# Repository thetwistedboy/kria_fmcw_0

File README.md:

# kria_fmcw_0
Carrier for Kria K24 SoM. Hardware to support FMCW radar playing.

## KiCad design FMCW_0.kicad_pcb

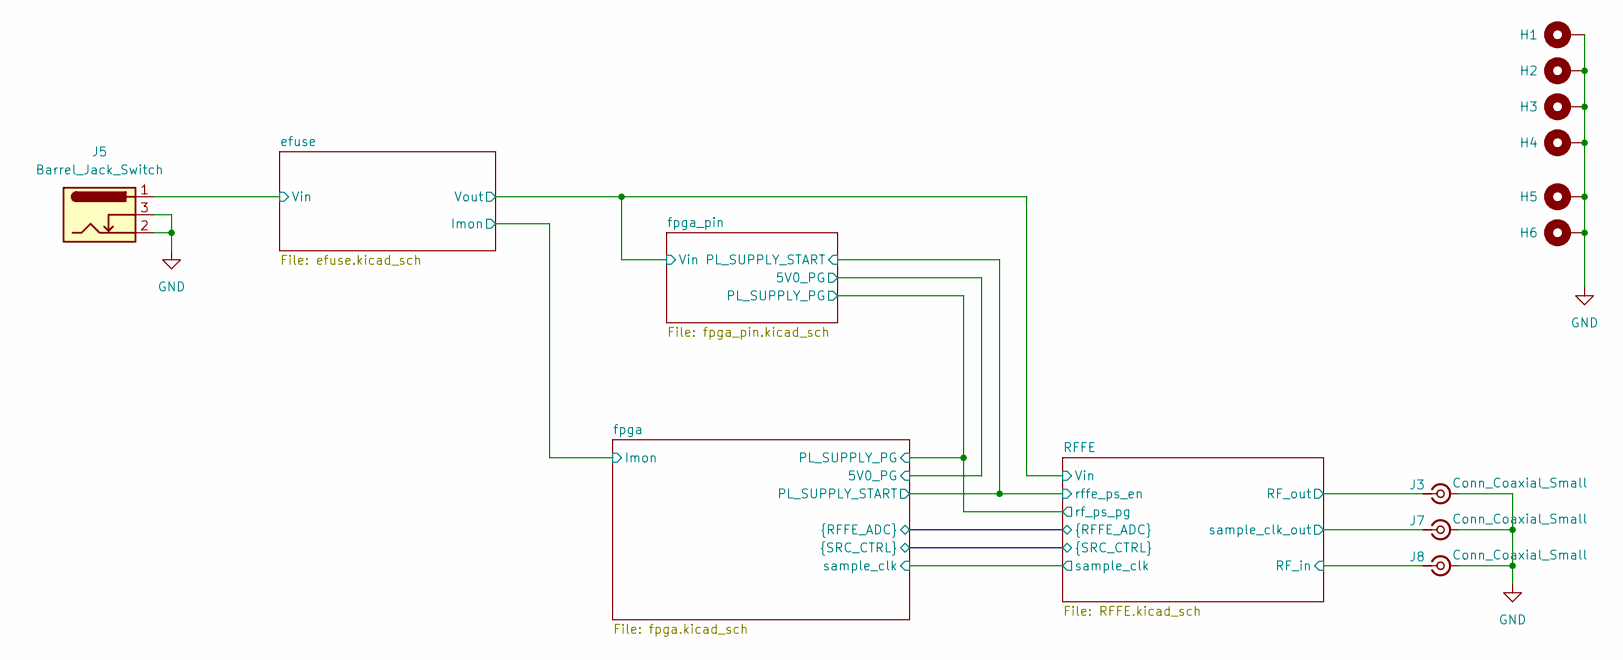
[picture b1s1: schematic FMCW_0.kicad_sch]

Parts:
H1, H2, H3, H4, H5, H6: MountingHole_Pad; MountingHole_3.2mm_M3_DIN965_Pad
J3, J7, J8: Conn_Coaxial_Small; SMA_Samtec_SMA-J-P-H-ST-EM1_EdgeMount
J5: Barrel_Jack_Switch; BarrelJack_Wuerth_6941xx301002; Digikey PN 732-5934-ND

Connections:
/RFFE/RF_in: J8.1 (In); also elsewhere on the board
/RFFE/RF_out: J3.1 (In); also elsewhere on the board
/RFFE/sample_clk_out: J7.1 (In); also elsewhere on the board
/efuse/Vin: J5.1; also elsewhere on the board
GND: H1.1 (1_1), H2.1 (1_1), H3.1 (1_1), H4.1 (1_1), H5.1 (1_1), H6.1 (1_1), J3.2 (Ext), J5.2, J5.3, J7.2 (Ext), J8.2 (Ext); also elsewhere on the board

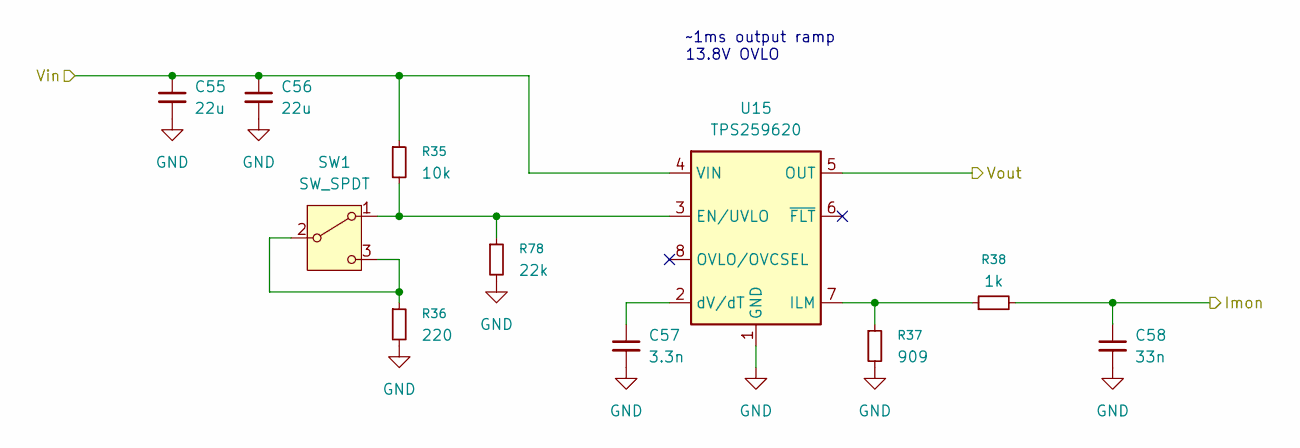
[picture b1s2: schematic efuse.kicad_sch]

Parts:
C55, C56: 22u; C_0805_2012Metric; Digikey PN 587-6359-1-ND
C57: 3.3n; C_0402_1005Metric; Digikey PN 1276-1552-1-ND
C58: 33n; C_0402_1005Metric; Digikey PN 587-3466-1-ND
R35: 10k; R_0402_1005Metric; Digikey PN RMCF0402FT10K0CT-ND
R36: 220; R_0402_1005Metric; Digikey PN 311-220LRCT-ND
R37: 909; R_0402_1005Metric; Digikey PN YAG3256CT-ND
R38: 1k; R_0402_1005Metric; Digikey PN 311-1.00KLRCT-ND
R78: 22k; R_0402_1005Metric; Digikey PN RMCF0402FT10K0CT-ND
SW1: SW_SPDT; SW_Slide_SPDT_Angled_CK_OS102011MA1Q; Digikey PN CKN9559-ND
U15: TPS259620; TI_SO-PowerPAD-8; Digikey PN 296-TPS259620DDARCT-ND

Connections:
/RFFE/Vin: U15.5 (OUT); also elsewhere on the board
/efuse/Imon: C58.1, R38.2; also elsewhere on the board
/efuse/Vin: C55.1, C56.1, R35.1, U15.4 (VIN); also elsewhere on the board
GND: C55.2, C56.2, C57.2, C58.2, R36.2, R37.2, R78.2, U15.1 (GND), U15.9 (GND); also elsewhere on the board
unnamed: R35.2, R78.1, SW1.1 (A), U15.3 (EN/UVLO)
unnamed: R36.1, SW1.2 (B), SW1.3 (C)
unnamed: R37.1, R38.1, U15.7 (ILM)
unnamed: C57.1, U15.2 (dV/dT)

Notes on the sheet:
~1ms output ramp 13.8V OVLO

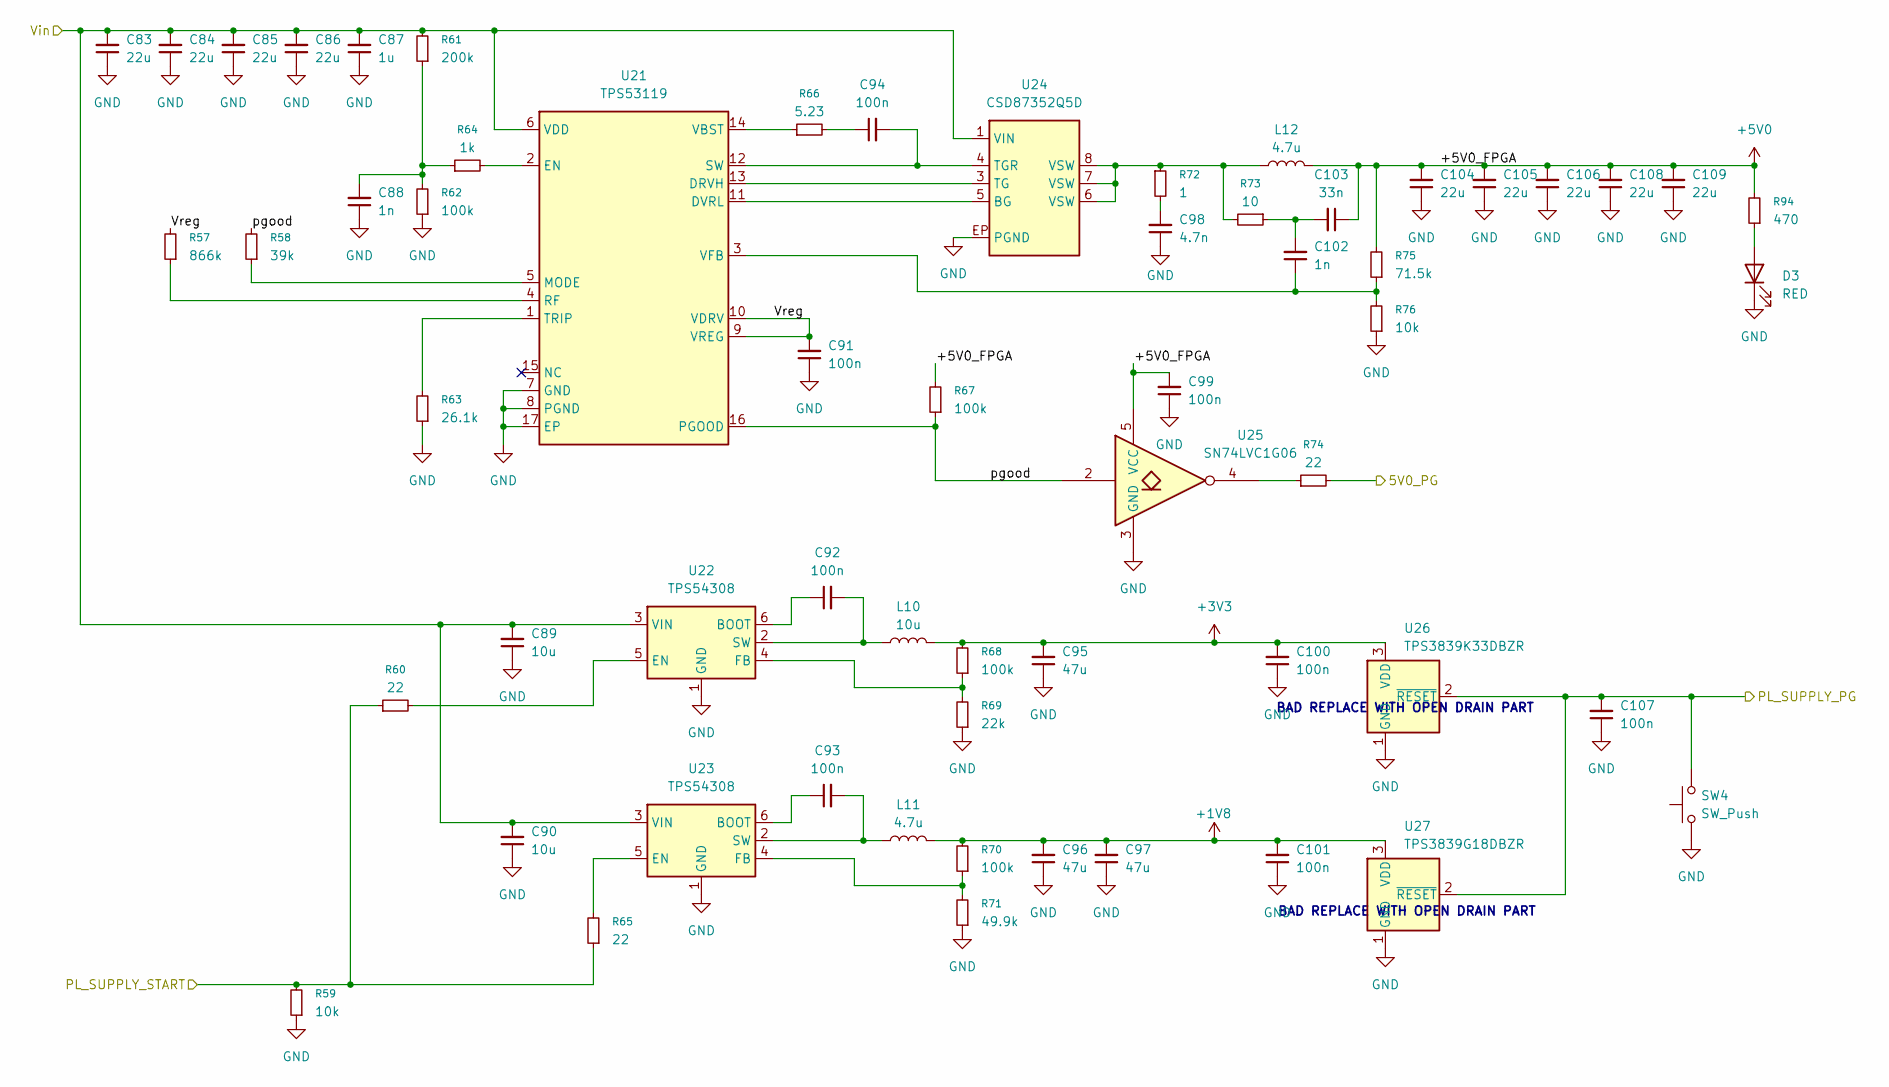
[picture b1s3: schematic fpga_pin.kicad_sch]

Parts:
C83, C84, C85, C86: 22u; C_1210_3225Metric; Digikey PN 587-5951-1-ND
C87: 1u; C_0402_1005Metric; Digikey PN 1276-1067-1-ND
C88, C102: 1n; C_0402_1005Metric; Digikey PN 490-3244-1-ND
C89, C90: 10u; C_0603_1608Metric; Digikey PN 490-7202-1-ND
C91, C92, C93, C94, C99, C100, C101, C107: 100n; C_0402_1005Metric; Digikey PN 1276-1043-1-ND
C95, C96, C97: 47u; C_0805_2012Metric; Digikey PN 490-13249-1-ND
C98: 4.7n; C_0402_1005Metric; Digikey PN 490-1308-1-ND
C103: 33n; C_0402_1005Metric; Digikey PN 587-3466-1-ND
C104, C105, C106, C108, C109: 22u; C_0805_2012Metric; Digikey PN 587-5466-1-ND
D3: RED; LED_0603_1608Metric; Digikey PN 160-1436-1-ND
L10: 10u; L_Wuerth_MAPI-4030; Digikey PN 732-11206-1-ND
L11: 4.7u; L_Wuerth_MAPI-4020; Digikey PN 732-11316-1-ND
L12: 4.7u; L_Wuerth_XHMI-6060; Digikey PN 732-744393445047CT-ND
R57: 866k; R_0402_1005Metric; Digikey PN RMCF0402FT866KCT-ND
R58: 39k; R_0402_1005Metric; Digikey PN 311-39.0KLRCT-ND
R59, R76: 10k; R_0402_1005Metric; Digikey PN RMCF0402FT10K0CT-ND
R60, R65, R74: 22; R_0402_1005Metric; Digikey PN 541-22.0LCT-ND
R61: 200k; R_0402_1005Metric; Digikey PN 311-200KLRCT-ND
R62, R67, R68, R70: 100k; R_0402_1005Metric; Digikey PN 311-100KLRCT-ND
R63: 26.1k; R_0402_1005Metric; Digikey PN 311-26.1KLRCT-ND
R64: 1k; R_0402_1005Metric; Digikey PN 311-1.00KLRCT-ND
R66: 5.23; R_0402_1005Metric; Digikey PN 541-5.23LLCT-ND
R69: 22k; R_0402_1005Metric; Digikey PN RMCF0402FT10K0CT-ND
R71: 49.9k; R_0402_1005Metric; Digikey PN P49.9KLCT-ND
R72: 1; R_0402_1005Metric; Digikey PN 541-1.00LLCT-ND
R73: 10; R_0402_1005Metric; Digikey PN 311-10.0LRCT-ND
R75: 71.5k; R_0402_1005Metric; Digikey PN RMCF0402FT71K5CT-ND
R94: 470; R_0402_1005Metric; Digikey PN 311-470LRCT-ND
SW4: SW_Push; SW_Push_1P1T_NO_CK_KMR2; Digikey PN 108-KMR211GLFSCT-ND
U21: TPS53119; VQFN-16-1EP_3x3mm_P0.5mm_EP1.45x1.45mm; Digikey PN 296-51985-1-ND
U22, U23: TPS54308; SOT-23-6; Digikey PN 296-46237-1-ND
U24: CSD87352Q5D; Texas_8-LSON_5x6mm; Digikey PN 296-29161-1-ND
U25: SN74LVC1G06; SOT-353_SC-70-5; Digikey PN 296-8484-1-ND
U26: TPS3839K33DBZR; SOT-23; Digikey PN 296-35471-1-ND
U27: TPS3839G18DBZR; SOT-23; Digikey PN 296-40761-1-ND

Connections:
+1V8: C96.2, C97.2, C101.2, L11.2, R70.2, U27.3 (VDD); also elsewhere on the board
+3V3: C95.2, C100.2, L10.2, R68.2, U26.3 (VDD); also elsewhere on the board
+5V0: C99.2, C103.1, C104.2, C105.2, C106.2, C108.2, C109.2, L12.2, R67.2, R75.2, R94.2, U25.5 (VCC); also elsewhere on the board
/RFFE/Vin: C83.2, C84.2, C85.2, C86.2, C87.2, C89.2, C90.2, R61.2, U21.6 (VDD), U22.3 (VIN), U23.3 (VIN), U24.1 (VIN); also elsewhere on the board
/RFFE/rf_ps_pg: C107.2, SW4.2, U26.2 (~RESET), U27.2 (~RESET); also elsewhere on the board
/RFFE/rffe_ps_en: R59.2, R60.1, R65.1; also elsewhere on the board
/fpga/5V0_PG: R74.2; also elsewhere on the board
/fpga_pin/Vreg: C91.2, R57.2, U21.9 (VREG), U21.10 (VDRV)
/fpga_pin/pgood: R58.2, R67.1, U21.16 (PGOOD), U25.2
GND: C83.1, C84.1, C85.1, C86.1, C87.1, C88.1, C89.1, C90.1, C91.1, C95.1, C96.1, C97.1, C98.1, C99.1, C100.1, C101.1, C104.1, C105.1, C106.1, C107.1, C108.1, C109.1, D3.1 (K), R59.1, R62.1, R63.1, R69.1, R71.1, R76.1, SW4.1, U21.7 (GND), U21.8 (PGND), U21.17 (EP), U22.1 (GND), U23.1 (GND), U24.EP (PGND), U25.3 (GND), U26.1 (GND), U27.1 (GND); also elsewhere on the board
unnamed: C88.2, R61.1, R62.2, R64.1
unnamed: C94.1, R66.2
unnamed: C98.2, R72.2
unnamed: C102.2, C103.2, R73.1
unnamed: D3.2 (A), R94.1
unnamed: L12.1, R72.1, R73.2, U24.6 (VSW), U24.7 (VSW), U24.8 (VSW)
unnamed: R74.1, U25.4
unnamed: U21.13 (DRVH), U24.3 (TG)
unnamed: U21.11 (DVRL), U24.5 (BG)
unnamed: R64.2, U21.2 (EN)
unnamed: R58.1, U21.5 (MODE)
unnamed: R57.1, U21.4 (RF)
unnamed: C94.2, U21.12 (SW), U24.4 (TGR)
unnamed: R63.2, U21.1 (TRIP)
unnamed: R66.1, U21.14 (VBST)
unnamed: C102.1, R75.1, R76.2, U21.3 (VFB)
unnamed: C92.1, U22.6 (BOOT)
unnamed: R60.2, U22.5 (EN)
unnamed: R68.1, R69.2, U22.4 (FB)
unnamed: C92.2, L10.1, U22.2 (SW)
unnamed: C93.1, U23.6 (BOOT)
unnamed: R65.2, U23.5 (EN)
unnamed: R70.1, R71.2, U23.4 (FB)
unnamed: C93.2, L11.1, U23.2 (SW)

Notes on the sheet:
BAD REPLACE WITH OPEN DRAIN PART

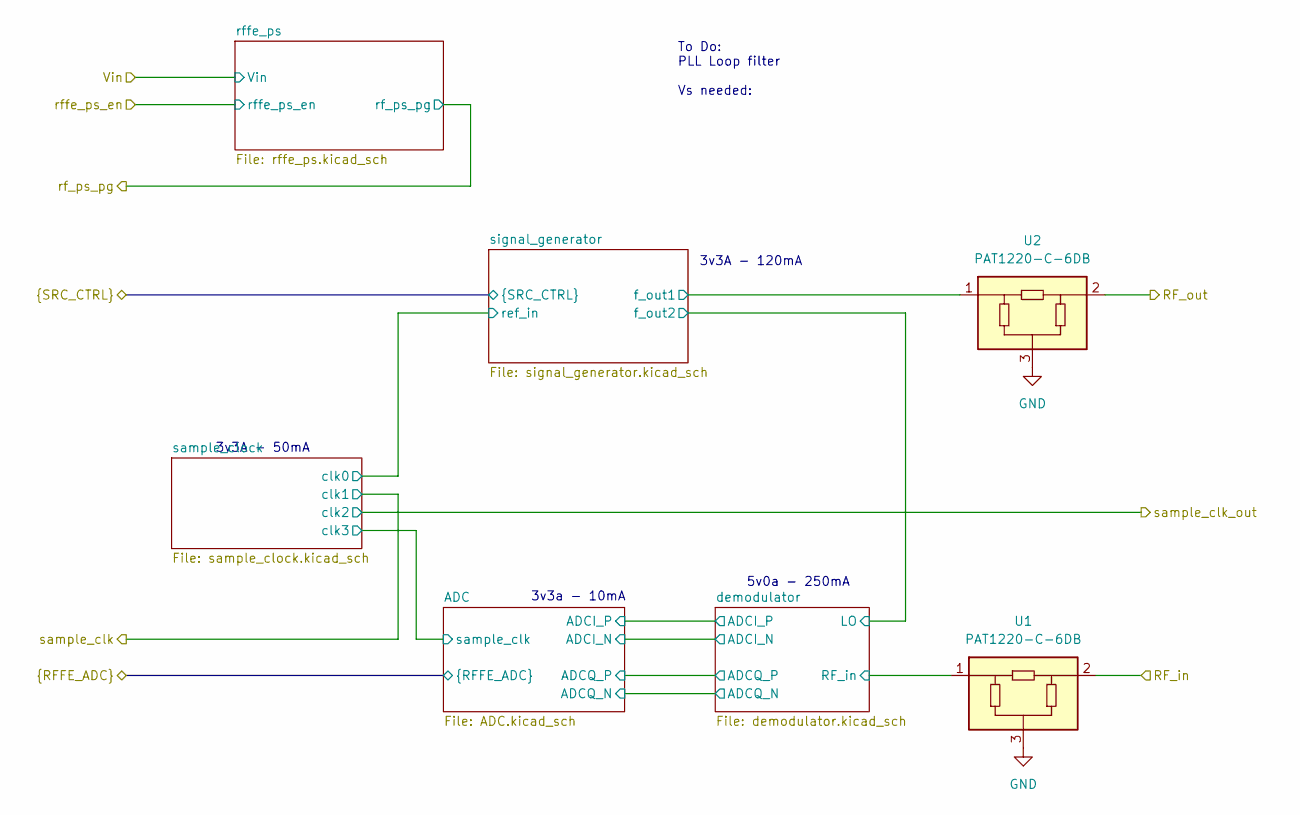
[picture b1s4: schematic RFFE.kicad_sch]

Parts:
U1, U2: PAT1220-C-6DB; RF_Attenuator_Susumu_PAT1220; Digikey PN PAT126CT-ND

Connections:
/RFFE/RF_in: U1.2; also elsewhere on the board
/RFFE/RF_out: U2.2; also elsewhere on the board
/RFFE/demodulator/RF_in: U1.1; also elsewhere on the board
/RFFE/signal_generator/f_out1: U2.1; also elsewhere on the board
GND: U1.3, U2.3; also elsewhere on the board

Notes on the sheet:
5v0a - 250mA
To Do: PLL Loop filter Vs needed:
3v3A - 50mA
3v3A - 120mA
3v3a - 10mA

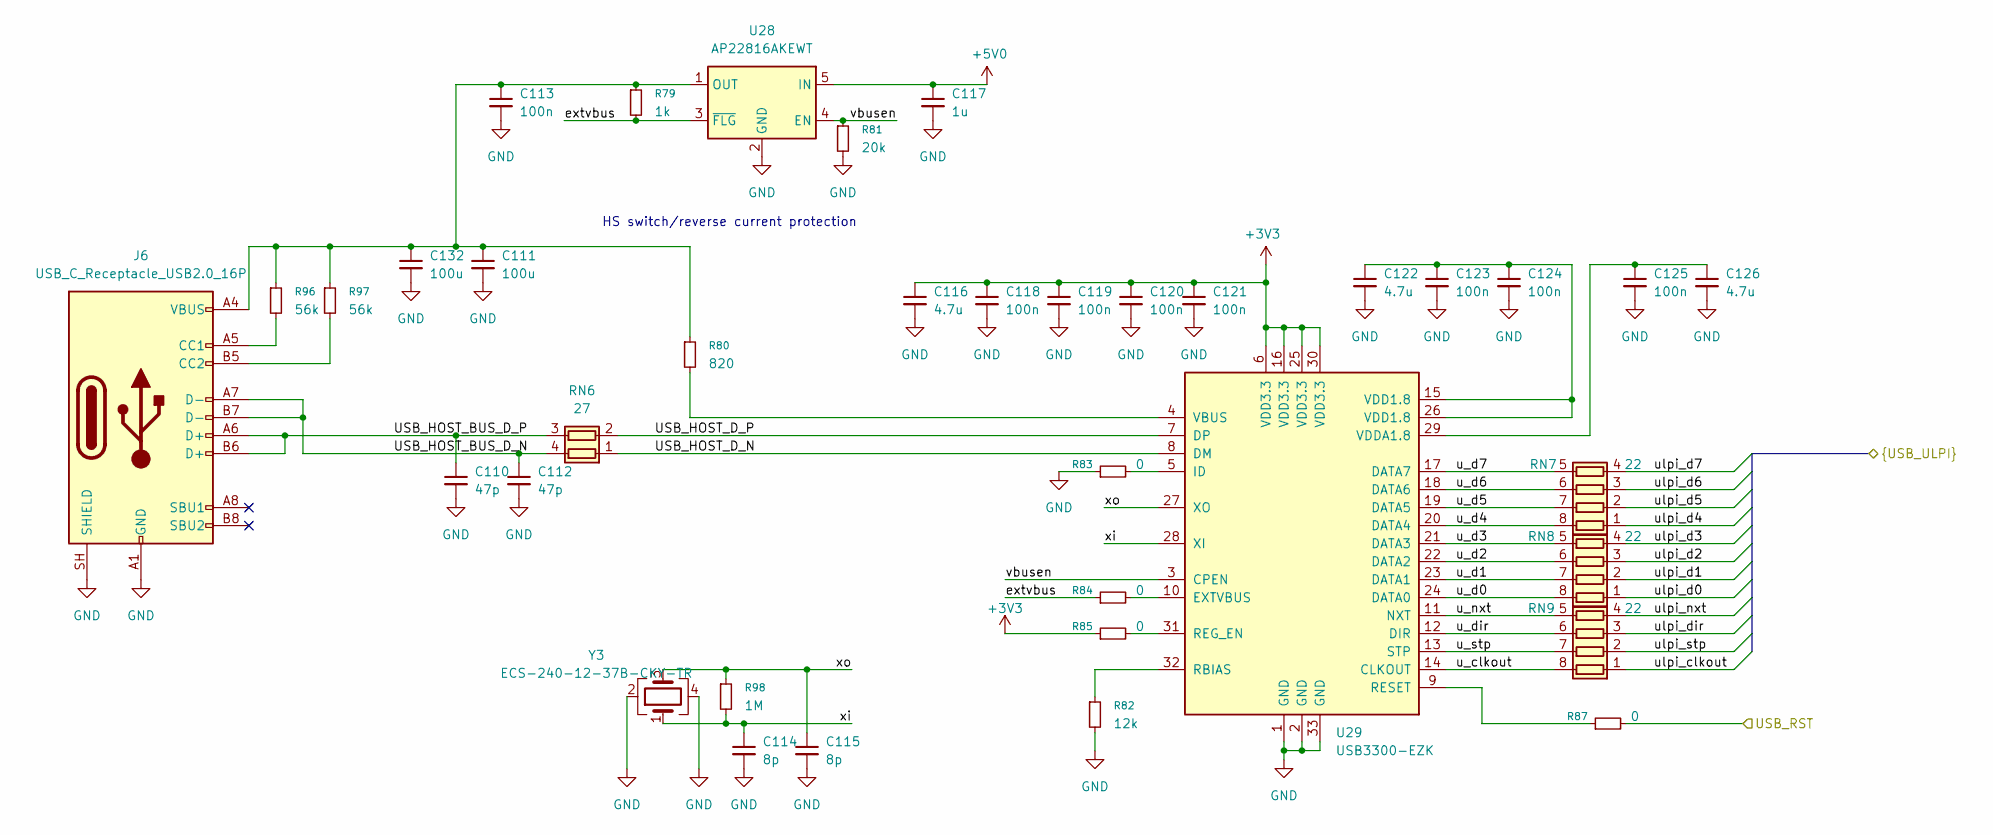
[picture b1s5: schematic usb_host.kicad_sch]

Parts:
C110, C112: 47p; C_0402_1005Metric; Digikey PN 490-5942-1-ND
C111, C132: 100u; C_1210_3225Metric; Digikey PN 490-10534-1-ND
C113, C118, C119, C120, C121, C123, C124, C125: 100n; C_0402_1005Metric; Digikey PN 1276-1043-1-ND
C114, C115: 8p; C_0402_1005Metric; Digikey PN 1276-CL05C080DB51PNCCT-ND
C116, C122, C126: 4.7u; C_0402_1005Metric; Digikey PN 490-14306-1-ND
C117: 1u; C_0402_1005Metric; Digikey PN 1276-1067-1-ND
J6: USB_C_Receptacle_USB2.0_16P; USB_C_Receptacle_GCT_USB4105-xx-A_16P_TopMnt_Horizontal; Digikey PN 2073-USB4215-03-ACT-ND
R79: 1k; R_0402_1005Metric; Digikey PN 311-1.00KLRCT-ND
R80: 820; R_0402_1005Metric; Digikey PN 311-820LRCT-ND
R81: 20k; R_0402_1005Metric; Digikey PN 311-20.0KLRCT-ND
R82: 12k; R_0402_1005Metric; Digikey PN 311-12.0KLRCT-ND
R83, R84, R85, R87: 0; R_0402_1005Metric; Digikey PN 311-0.0JRCT-ND
R96, R97: 56k; R_0402_1005Metric; Digikey PN 311-20.0KLRCT-ND
R98: 1M; R_0402_1005Metric; Digikey PN 311-1.00MLRCT-ND
RN6: 27; R_Array_Convex_2x0402; Digikey PN Y5270CT-ND
RN7, RN8, RN9: 22; R_Array_Convex_4x0402; Digikey PN Y7220CT-ND
U28: AP22816AKEWT; SOT-23-5; Digikey PN 31-AP22816AKEWT-7CT-ND
U29: USB3300-EZK; QFN-32-1EP_5x5mm_P0.5mm_EP3.45x3.45mm; Digikey PN 638-1034-ND
Y3: ECS-240-12-37B-CKY-TR; Crystal_SMD_2016-4Pin_2.0x1.6mm; Digikey PN XC3064TR-ND

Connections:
+3V3: C116.1, C118.1, C119.1, C120.1, C121.1, R85.1, U29.6 (VDD3.3), U29.16 (VDD3.3), U29.25 (VDD3.3), U29.30 (VDD3.3); also elsewhere on the board
+5V0: C117.1, U28.5 (IN); also elsewhere on the board
/fpga/fpga_ja/ulpi_clkout: RN9.1 (R1.1); also elsewhere on the board
/fpga/fpga_ja/ulpi_d0: RN8.1 (R1.1); also elsewhere on the board
/fpga/fpga_ja/ulpi_d1: RN8.2 (R2.1); also elsewhere on the board
/fpga/fpga_ja/ulpi_d2: RN8.3 (R3.1); also elsewhere on the board
/fpga/fpga_ja/ulpi_d3: RN8.4 (R4.1); also elsewhere on the board
/fpga/fpga_ja/ulpi_d4: RN7.1 (R1.1); also elsewhere on the board
/fpga/fpga_ja/ulpi_d5: RN7.2 (R2.1); also elsewhere on the board
/fpga/fpga_ja/ulpi_d6: RN7.3 (R3.1); also elsewhere on the board
/fpga/fpga_ja/ulpi_d7: RN7.4 (R4.1); also elsewhere on the board
/fpga/fpga_ja/ulpi_dir: RN9.3 (R3.1); also elsewhere on the board
/fpga/fpga_ja/ulpi_nxt: RN9.4 (R4.1); also elsewhere on the board
/fpga/fpga_ja/ulpi_stp: RN9.2 (R2.1); also elsewhere on the board
/fpga/fpga_ja/usb_reset: R87.2; also elsewhere on the board
/fpga/usb_host/USB_HOST_BUS_D_N: C112.1, J6.A7 (D-), J6.B7 (D-), RN6.4 (R1.2)
/fpga/usb_host/USB_HOST_BUS_D_P: C110.1, J6.A6 (D+), J6.B6 (D+), RN6.3 (R2.2)
/fpga/usb_host/USB_HOST_D_N: RN6.1 (R1.1), U29.8 (DM)
/fpga/usb_host/USB_HOST_D_P: RN6.2 (R2.1), U29.7 (DP)
/fpga/usb_host/extvbus: R79.2, R84.1, U28.3 (~FLG)
/fpga/usb_host/u_clkout: RN9.8 (R1.2), U29.14 (CLKOUT)
/fpga/usb_host/u_d0: RN8.8 (R1.2), U29.24 (DATA0)
/fpga/usb_host/u_d1: RN8.7 (R2.2), U29.23 (DATA1)
/fpga/usb_host/u_d2: RN8.6 (R3.2), U29.22 (DATA2)
/fpga/usb_host/u_d3: RN8.5 (R4.2), U29.21 (DATA3)
/fpga/usb_host/u_d4: RN7.8 (R1.2), U29.20 (DATA4)
/fpga/usb_host/u_d5: RN7.7 (R2.2), U29.19 (DATA5)
/fpga/usb_host/u_d6: RN7.6 (R3.2), U29.18 (DATA6)
/fpga/usb_host/u_d7: RN7.5 (R4.2), U29.17 (DATA7)
/fpga/usb_host/u_dir: RN9.6 (R3.2), U29.12 (DIR)
/fpga/usb_host/u_nxt: RN9.5 (R4.2), U29.11 (NXT)
/fpga/usb_host/u_stp: RN9.7 (R2.2), U29.13 (STP)
/fpga/usb_host/vbusen: R81.1, U28.4 (EN), U29.3 (CPEN)
/fpga/usb_host/xi: C114.1, R98.2, U29.28 (XI), Y3.1
/fpga/usb_host/xo: C115.1, R98.1, U29.27 (XO), Y3.3
GND: C110.2, C111.2, C112.2, C113.2, C114.2, C115.2, C116.2, C117.2, C118.2, C119.2, C120.2, C121.2, C122.2, C123.2, C124.2, C125.2, C126.2, C132.2, J6.A1 (GND), J6.A12 (GND), J6.B1 (GND), J6.B12 (GND), J6.SH (SHIELD), R81.2, R82.2, R83.1, U28.2 (GND), U29.1 (GND), U29.2 (GND), U29.33 (GND), Y3.2, Y3.4; also elsewhere on the board
unnamed: C122.1, C123.1, C124.1, U29.15 (VDD1.8), U29.26 (VDD1.8)
unnamed: J6.A5 (CC1), R96.2
unnamed: J6.B5 (CC2), R97.2
unnamed: C111.1, C113.1, C132.1, J6.A4 (VBUS), J6.A9 (VBUS), J6.B4 (VBUS), J6.B9 (VBUS), R79.1, R80.1, R96.1, R97.1, U28.1 (OUT)
unnamed: R84.2, U29.10 (EXTVBUS)
unnamed: R83.2, U29.5 (ID)
unnamed: R82.1, U29.32 (RBIAS)
unnamed: R85.2, U29.31 (REG_EN)
unnamed: R87.1, U29.9 (RESET)
unnamed: R80.2, U29.4 (VBUS)
unnamed: C125.1, C126.1, U29.29 (VDDA1.8)

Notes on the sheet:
HS switch/reverse current protection

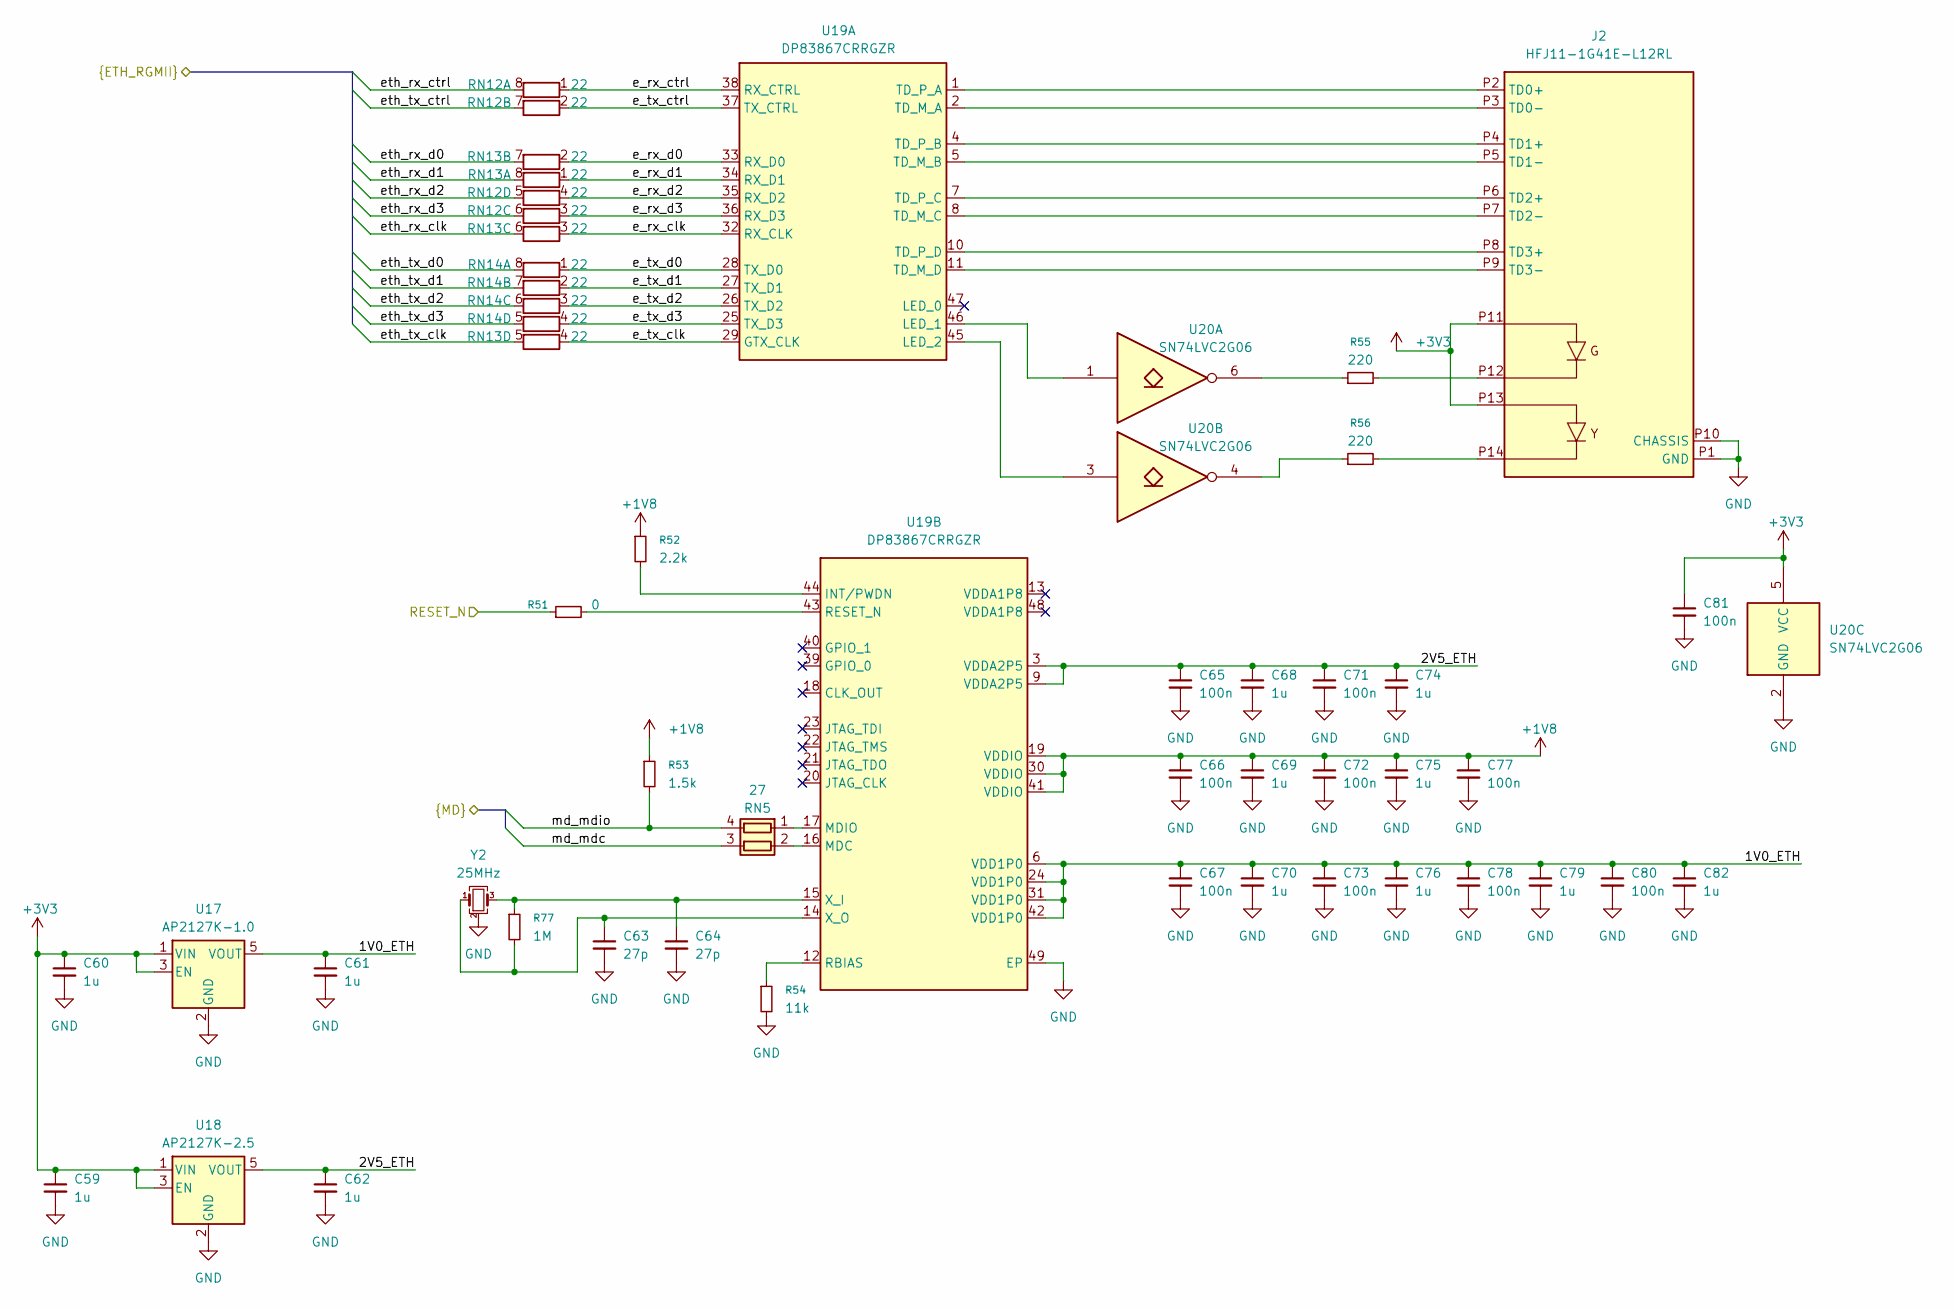
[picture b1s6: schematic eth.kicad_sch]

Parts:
C59, C60, C61, C62, C68, C69, C70, C74, C75, C76, C79, C82: 1u; C_0402_1005Metric; Digikey PN 1276-1067-1-ND
C63, C64: 27p; C_0402_1005Metric; Digikey PN 490-5869-1-ND
C65, C66, C67, C71, C72, C73, C77, C78, C80, C81: 100n; C_0402_1005Metric; Digikey PN 1276-1043-1-ND
J2: HFJ11-1G41E-L12RL; Digikey PN 5843-HFJ11-1G41E-L12RL-ND
R51: 0; R_0402_1005Metric; Digikey PN 311-0.0JRCT-ND
R52: 2.2k; R_0402_1005Metric; Digikey PN RMCF0402FT2K20CT-ND
R53: 1.5k; R_0402_1005Metric; Digikey PN P1.50KLCT-ND
R54: 11k; R_0402_1005Metric; Digikey PN P11KDCCT-ND
R55, R56: 220; R_0402_1005Metric; Digikey PN 311-220LRCT-ND
R77: 1M; R_0402_1005Metric; Digikey PN 311-1.00MLRCT-ND
RN5: 27; R_Array_Convex_2x0402; Digikey PN Y5270CT-ND
RN12, RN13, RN14: 22; R_Array_Convex_4x0402; Digikey PN Y7220CT-ND
U17: AP2127K-1.0; SOT-23-5; Digikey PN 31-AP2127K-1.0TRG1CT-ND
U18: AP2127K-2.5; SOT-23-5; Digikey PN 31-AP2127K-2.5TRG1CT-ND
U19: DP83867CRRGZR; VQFN-48-1EP_7x7mm_P0.5mm_EP4.1x4.1mm; Digikey PN 296-51057-1-ND
U20: SN74LVC2G06; SOT-363_SC-70-6; Digikey PN 296-13493-1-ND
Y2: 25MHz; Crystal_SMD_3225-4Pin_3.2x2.5mm; Digikey PN 535-10275-1-ND

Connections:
+1V8: C66.1, C69.1, C72.1, C75.1, C77.1, R52.1, R53.1, U19.19 (VDDIO), U19.30 (VDDIO), U19.41 (VDDIO); also elsewhere on the board
+3V3: C59.1, C60.1, C81.1, J2.P11, J2.P13, U17.1 (VIN), U17.3 (EN), U18.1 (VIN), U18.3 (EN), U20.5 (VCC); also elsewhere on the board
/RFFE/rf_ps_pg: R51.1; also elsewhere on the board
/fpga/eth/1V0_ETH: C61.1, C67.1, C70.1, C73.1, C76.1, C78.1, C79.1, C80.1, C82.1, U17.5 (VOUT), U19.6 (VDD1P0), U19.24 (VDD1P0), U19.31 (VDD1P0), U19.42 (VDD1P0)
/fpga/eth/2V5_ETH: C62.1, C65.1, C68.1, C71.1, C74.1, U18.5 (VOUT), U19.3 (VDDA2P5), U19.9 (VDDA2P5)
/fpga/eth/e_rx_clk: RN13.3 (R3.1), U19.32 (RX_CLK)
/fpga/eth/e_rx_ctrl: RN12.1 (R1.1), U19.38 (RX_CTRL)
/fpga/eth/e_rx_d0: RN13.2 (R2.1), U19.33 (RX_D0)
/fpga/eth/e_rx_d1: RN13.1 (R1.1), U19.34 (RX_D1)
/fpga/eth/e_rx_d2: RN12.4 (R4.1), U19.35 (RX_D2)
/fpga/eth/e_rx_d3: RN12.3 (R3.1), U19.36 (RX_D3)
/fpga/eth/e_tx_clk: RN13.4 (R4.1), U19.29 (GTX_CLK)
/fpga/eth/e_tx_ctrl: RN12.2 (R2.1), U19.37 (TX_CTRL)
/fpga/eth/e_tx_d0: RN14.1 (R1.1), U19.28 (TX_D0)
/fpga/eth/e_tx_d1: RN14.2 (R2.1), U19.27 (TX_D1)
/fpga/eth/e_tx_d2: RN14.3 (R3.1), U19.26 (TX_D2)
/fpga/eth/e_tx_d3: RN14.4 (R4.1), U19.25 (TX_D3)
/fpga/eth/eth_rx_clk: RN13.6 (R3.2); also elsewhere on the board
/fpga/eth/eth_rx_ctrl: RN12.8 (R1.2); also elsewhere on the board
/fpga/eth/eth_rx_d0: RN13.7 (R2.2); also elsewhere on the board
/fpga/eth/eth_rx_d1: RN13.8 (R1.2); also elsewhere on the board
/fpga/eth/eth_rx_d2: RN12.5 (R4.2); also elsewhere on the board
/fpga/eth/eth_rx_d3: RN12.6 (R3.2); also elsewhere on the board
/fpga/eth/eth_tx_clk: RN13.5 (R4.2); also elsewhere on the board
/fpga/eth/eth_tx_ctrl: RN12.7 (R2.2); also elsewhere on the board
/fpga/eth/eth_tx_d0: RN14.8 (R1.2); also elsewhere on the board
/fpga/eth/eth_tx_d1: RN14.7 (R2.2); also elsewhere on the board
/fpga/eth/eth_tx_d2: RN14.6 (R3.2); also elsewhere on the board
/fpga/eth/eth_tx_d3: RN14.5 (R4.2); also elsewhere on the board
/fpga/eth/md_mdc: RN5.3 (R2.2); also elsewhere on the board
/fpga/eth/md_mdio: R53.2, RN5.4 (R1.2); also elsewhere on the board
GND: C59.2, C60.2, C61.2, C62.2, C63.2, C64.2, C65.2, C66.2, C67.2, C68.2, C69.2, C70.2, C71.2, C72.2, C73.2, C74.2, C75.2, C76.2, C77.2, C78.2, C79.2, C80.2, C81.2, C82.2, J2.P1 (GND), J2.P10 (CHASSIS), R54.2, U17.2 (GND), U18.2 (GND), U19.49 (EP), U20.2 (GND), Y2.2 (G), Y2.4 (G); also elsewhere on the board
unnamed: J2.P12, R55.2
unnamed: J2.P14, R56.2
unnamed: J2.P2 (TD0+), U19.1 (TD_P_A)
unnamed: J2.P3 (TD0-), U19.2 (TD_M_A)
unnamed: J2.P4 (TD1+), U19.4 (TD_P_B)
unnamed: J2.P5 (TD1-), U19.5 (TD_M_B)
unnamed: J2.P6 (TD2+), U19.7 (TD_P_C)
unnamed: J2.P7 (TD2-), U19.8 (TD_M_C)
unnamed: J2.P8 (TD3+), U19.10 (TD_P_D)
unnamed: J2.P9 (TD3-), U19.11 (TD_M_D)
unnamed: R55.1, U20.6
unnamed: R56.1, U20.4
unnamed: RN5.1 (R1.1), U19.17 (MDIO)
unnamed: RN5.2 (R2.1), U19.16 (MDC)
unnamed: U19.46 (LED_1), U20.1
unnamed: U19.45 (LED_2), U20.3
unnamed: R52.2, U19.44 (INT/PWDN)
unnamed: R54.1, U19.12 (RBIAS)
unnamed: R51.2, U19.43 (RESET_N)
unnamed: C64.1, R77.1, U19.15 (X_I), Y2.3
unnamed: C63.1, R77.2, U19.14 (X_O), Y2.1

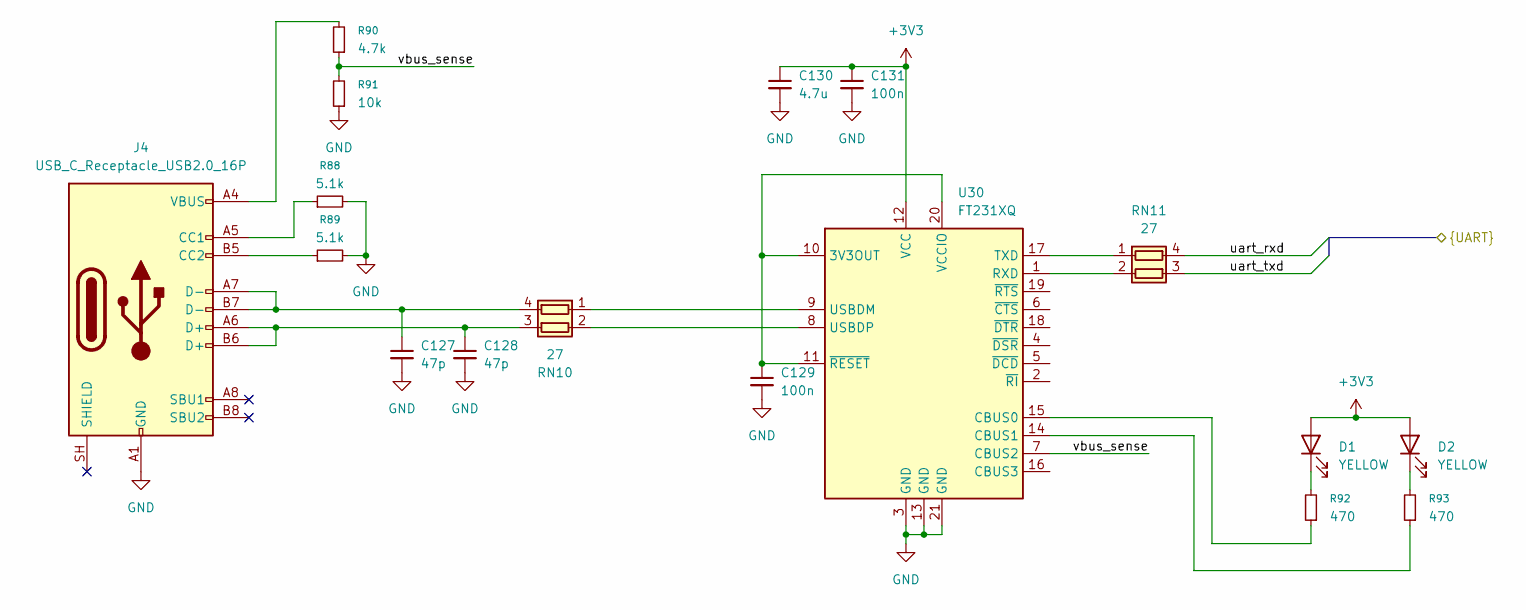
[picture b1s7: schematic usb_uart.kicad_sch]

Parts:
C127, C128: 47p; C_0402_1005Metric; Digikey PN 490-5942-1-ND
C129, C131: 100n; C_0402_1005Metric; Digikey PN 1276-1043-1-ND
C130: 4.7u; C_0603_1608Metric; Digikey PN 1276-2087-1-ND
D1, D2: YELLOW; LED_0603_1608Metric; Digikey PN 160-1437-1-ND
J4: USB_C_Receptacle_USB2.0_16P; USB_C_Receptacle_GCT_USB4105-xx-A_16P_TopMnt_Horizontal; Digikey PN 2073-USB4215-03-ACT-ND
R88, R89: 5.1k; R_0402_1005Metric; Digikey PN P5.10KLCT-ND
R90: 4.7k; R_0402_1005Metric; Digikey PN 311-4.7KJRCT-ND
R91: 10k; R_0402_1005Metric; Digikey PN RMCF0402FT10K0CT-ND
R92, R93: 470; R_0402_1005Metric; Digikey PN 311-470LRCT-ND
RN10, RN11: 27; R_Array_Convex_2x0402; Digikey PN Y5270CT-ND
U30: FT231XQ; QFN-20-1EP_4x4mm_P0.5mm_EP2.5x2.5mm

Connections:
+3V3: C130.1, C131.1, D1.2 (A), D2.2 (A), U30.12 (VCC); also elsewhere on the board
/fpga/fpga_ja/uart_rxd: RN11.4 (R1.2); also elsewhere on the board
/fpga/fpga_ja/uart_txd: RN11.3 (R2.2); also elsewhere on the board
/fpga/usb_uart/vbus_sense: R90.1, R91.2, U30.7 (CBUS2)
GND: C127.2, C128.2, C129.2, C130.2, C131.2, J4.A1 (GND), J4.A12 (GND), J4.B1 (GND), J4.B12 (GND), R88.2, R89.2, R91.1, U30.3 (GND), U30.13 (GND), U30.21 (GND); also elsewhere on the board
unnamed: D1.1 (K), R92.2
unnamed: D2.1 (K), R93.2
unnamed: J4.A5 (CC1), R88.1
unnamed: J4.B5 (CC2), R89.1
unnamed: J4.A4 (VBUS), J4.A9 (VBUS), J4.B4 (VBUS), J4.B9 (VBUS), R90.2
unnamed: RN10.1 (R1.1), U30.9 (USBDM)
unnamed: C127.1, J4.A7 (D-), J4.B7 (D-), RN10.4 (R1.2)
unnamed: RN10.2 (R2.1), U30.8 (USBDP)
unnamed: C128.1, J4.A6 (D+), J4.B6 (D+), RN10.3 (R2.2)
unnamed: RN11.1 (R1.1), U30.17 (TXD)
unnamed: RN11.2 (R2.1), U30.1 (RXD)
unnamed: C129.1, U30.10 (3V3OUT), U30.11 (~RESET), U30.20 (VCCIO)
unnamed: R92.1, U30.15 (CBUS0)
unnamed: R93.1, U30.14 (CBUS1)

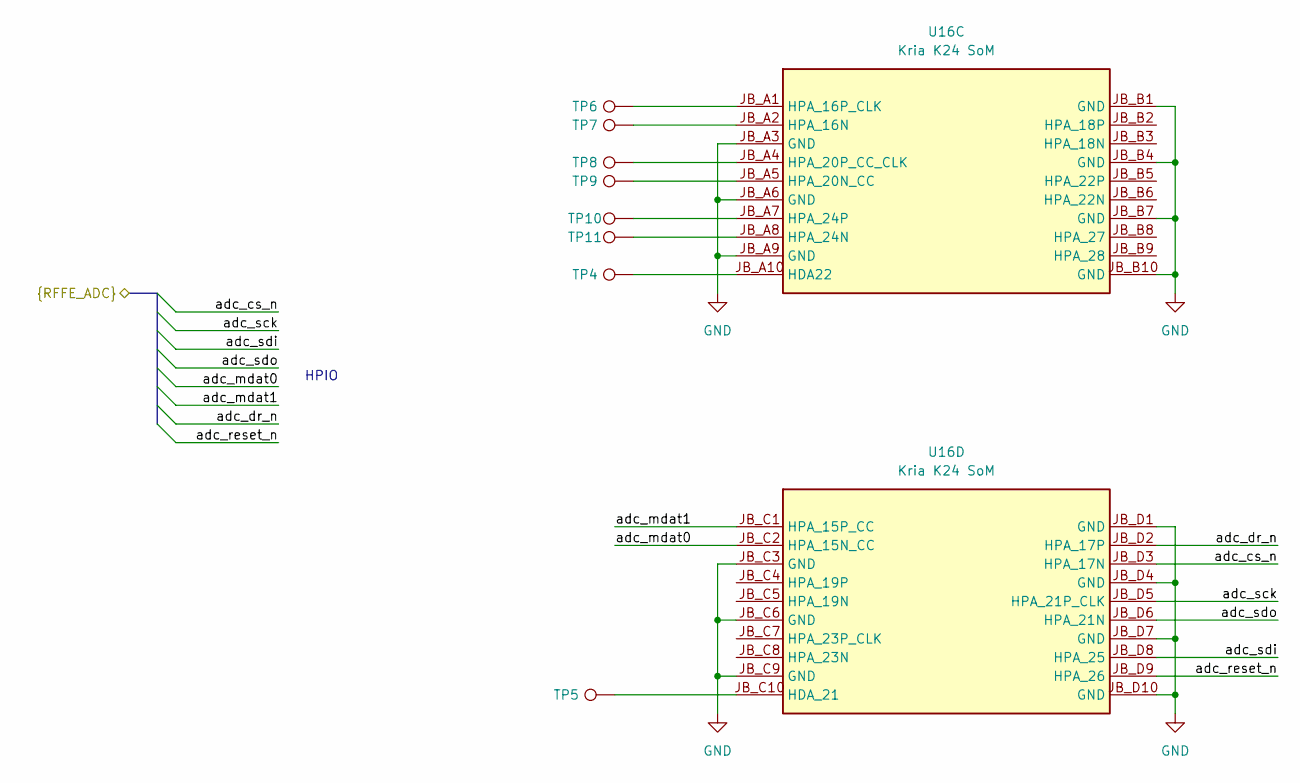
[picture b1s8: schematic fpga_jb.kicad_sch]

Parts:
TP4, TP5, TP6, TP7, TP8, TP9, TP10, TP11: TestPoint; TestPoint_Keystone_5015_Micro_Mini
U16: Kria K24 SoM; Kria_K24

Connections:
/RFFE/adc_cs_n: U16.JB_D3 (HPA_17N); also elsewhere on the board
/RFFE/adc_dr_n: U16.JB_D2 (HPA_17P); also elsewhere on the board
/RFFE/adc_mdat0: U16.JB_C2 (HPA_15N_CC); also elsewhere on the board
/RFFE/adc_mdat1: U16.JB_C1 (HPA_15P_CC); also elsewhere on the board
/RFFE/adc_reset_n: U16.JB_D9 (HPA_26); also elsewhere on the board
/RFFE/adc_sck: U16.JB_D5 (HPA_21P_CLK); also elsewhere on the board
/RFFE/adc_sdi: U16.JB_D8 (HPA_25); also elsewhere on the board
/RFFE/adc_sdo: U16.JB_D6 (HPA_21N); also elsewhere on the board
GND: U16.JB_A3 (GND), U16.JB_A6 (GND), U16.JB_A9 (GND), U16.JB_B1 (GND), U16.JB_B4 (GND), U16.JB_B7 (GND), U16.JB_B10 (GND), U16.JB_C3 (GND), U16.JB_C6 (GND), U16.JB_C9 (GND), U16.JB_D1 (GND), U16.JB_D4 (GND), U16.JB_D7 (GND), U16.JB_D10 (GND); also elsewhere on the board
unnamed: TP4.1 (1_1), U16.JB_A10 (HDA22)
unnamed: TP7.1 (1_1), U16.JB_A2 (HPA_16N)
unnamed: TP6.1 (1_1), U16.JB_A1 (HPA_16P_CLK)
unnamed: TP9.1 (1_1), U16.JB_A5 (HPA_20N_CC)
unnamed: TP8.1 (1_1), U16.JB_A4 (HPA_20P_CC_CLK)
unnamed: TP11.1 (1_1), U16.JB_A8 (HPA_24N)
unnamed: TP10.1 (1_1), U16.JB_A7 (HPA_24P)
unnamed: TP5.1 (1_1), U16.JB_C10 (HDA_21)

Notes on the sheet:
HPIO
